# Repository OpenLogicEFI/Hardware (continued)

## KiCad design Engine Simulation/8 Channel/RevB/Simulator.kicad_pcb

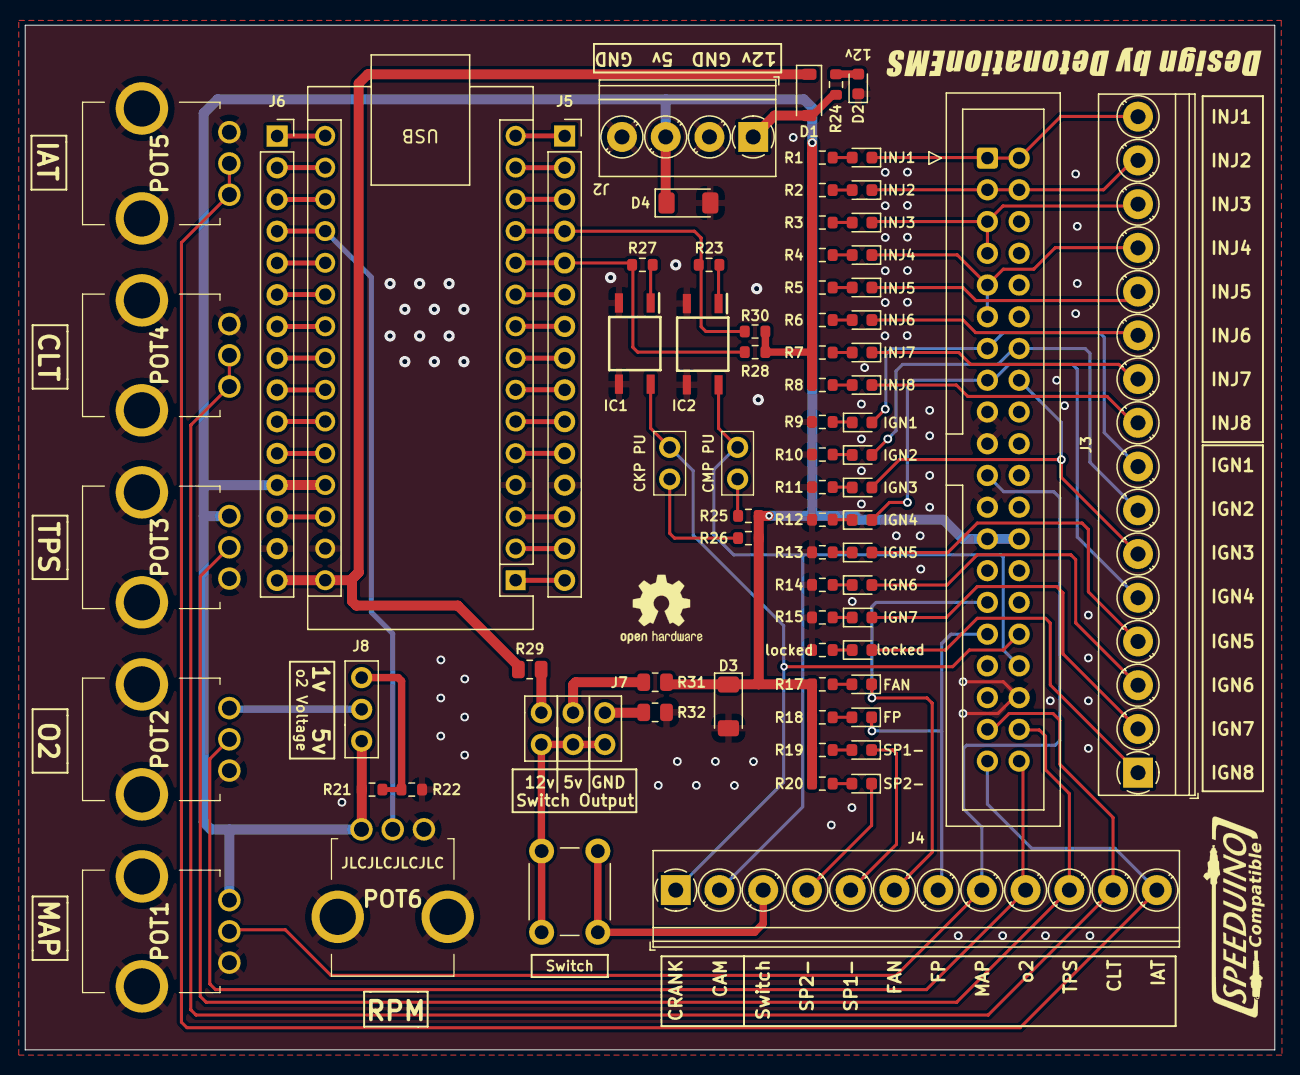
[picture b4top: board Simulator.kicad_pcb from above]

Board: 2 copper layers, 100.0 x 82.0 mm, 79 parts (0 on the bottom side), 89 nets.

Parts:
A1: Arduino_Nano_v3.x; Arduino_Nano
D1: B5819W; D_SOD-123
D2: 12v; LED_0603_1608Metric
D3, D4: ZMM5V6; D_MiniMELF
G1: Logo_Open_Hardware_Small; Design by 30mm
G2: Logo_Open_Hardware_Small; SpeeduinoCompatible-17mm
G3: Logo_Open_Hardware_Small; OSHW-Logo2_7.3x6mm_SilkScreen
IC1, IC2: EL357NB_TA_-G; SOP254P700X200-4N
J1: Conn_02x20_Counter_Clockwise; IDC-Header_2x20_P2.54mm_Vertical_Speeduino
J2: Conn_01x04; TerminalBlock_Phoenix_PT-1,5-4-3.5-H_1x04_P3.50mm_Horizontal
J3: Conn_01x08; TerminalBlock_Phoenix_PT-1,5-16-3.5-H_1x16_P3.50mm_Horizont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
J4: Conn_01x10; TerminalBlock_Phoenix_PT-1,5-12-3.5-H_1x12_P3.50mm_Horizont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
J5, J6: Conn_01x04; PinSocket_1x15_P2.54mm_Vertical
J7: Conn_01x03; PinSocket 2x03
J8: Conn_01x03; 3-PinSwitch
J9: CKP PU; 1x02-Proto
J10: CMP PU; 1x02-Proto
LED1: INJ1; LED_0603_1608Metric
LED2: INJ2; LED_0603_1608Metric
LED3: INJ3; LED_0603_1608Metric
LED4: INJ4; LED_0603_1608Metric
LED5: INJ5; LED_0603_1608Metric
LED6: INJ6; LED_0603_1608Metric
LED7: INJ7; LED_0603_1608Metric
LED8: INJ8; LED_0603_1608Metric
LED9: IGN1; LED_0603_1608Metric
LED10: IGN2; LED_0603_1608Metric
LED11: IGN3; LED_0603_1608Metric
LED12: IGN4; LED_0603_1608Metric
LED13: IGN5; LED_0603_1608Metric
LED14: IGN6; LED_0603_1608Metric
LED15: IGN7; LED_0603_1608Metric
LED16: locked; LED_0603_1608Metric
LED17: FAN; LED_0603_1608Metric
LED18: FP; LED_0603_1608Metric
LED19: SP1-; LED_0603_1608Metric
LED20: SP2-; LED_0603_1608Metric
POT1: IAT; RV09AF4020KB10K
POT2: CLT; RV09AF4020KB10K
POT3: MAP/SP1; RV09AF4020KB10K
POT4: TPS; RV09AF4020KB10K
POT5: o2; RV09AF4020KB10K
POT6: RPM; RV09AF4020KB10K
R1, R2, R3, R4, R5, R6, R7, R8, R9, R10, R11, R12, R13, R14, R15, R17, R18, R19, R20, R24, R25, R26, R28, R30: 1k; R_0603_1608Metric
R21, R23, R27: 470r; R_0603_1608Metric
R22: 100r; R_0603_1608Metric
R29, R31, R32: 0r; R_0805_2012Metric
SW1: Switch; SW_PUSH_6mm_H9.5mm
locked: 1k; R_0603_1608Metric

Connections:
12v-Unprotected: D1.2 (A), J2.1, R24.1
+3.3V: A1.17 (3V3), J6.2
+5V: A1.27 (+5V), D3.1 (K), D4.1 (K), J1.13, J1.28, J2.3, J6.12, J8.1, POT1.3, POT3.3, POT6.3, R1.1, R2.1, R3.1, R4.1, R5.1, R6.1, R7.1, R8.1, R17.1, R18.1, R19.1, R20.1, R21.1, R25.1, R26.1, R28.2, R30.2, R31.2
+12V: A1.30 (VIN), D1.1 (K), J6.15, R29.2
CAM: A1.12 (D9), J5.4, R23.2, R30.1
CAM-OUT: IC2.4 (C), J1.24, J4.2, J10.2
CLT: J1.19, J4.11, POT4.1, POT4.2
CRANK: A1.11 (D8), J5.5, R27.2, R28.1
CRANK-OUT: IC1.4 (C), J1.25, J4.1, J9.2
FAN: J1.15, J4.6, LED17.1 (K)
FP: J1.16, J4.7, LED18.1 (K)
GND: A1.4 (GND), A1.29 (GND), D2.1 (K), D3.2 (A), D4.2 (A), IC1.2 (K), IC1.3 (E), IC2.2 (K), IC2.3 (E), J1.9, J1.10, J1.12, J1.23, J2.2, J2.4, J5.12, J6.14, POT1.1, POT1.4 (Mounting_Tap), POT1.5 (Mounting_Tap), POT2.1, POT2.4 (Mounting_Tap), POT2.5 (Mounting_Tap), POT3.1, POT3.4 (Mounting_Tap), POT3.5 (Mounting_Tap), POT4.3, POT4.4 (Mounting_Tap), POT4.5 (Mounting_Tap), POT5.3, POT5.4 (Mounting_Tap), POT5.5 (Mounting_Tap), POT6.1, POT6.4 (Mounting_Tap), POT6.5 (Mounting_Tap), R9.1, R10.1, R11.1, R12.1, R13.1, R14.1, R15.1, R22.2, R32.1, locked.1
IAT: J1.20, J4.12, POT5.1, POT5.2
IGN1: J1.7, J3.8, LED9.2 (A)
IGN2: J1.34, J3.7, LED10.2 (A)
IGN3: J1.33, J3.6, LED11.2 (A)
IGN4: J1.8, J3.5, LED12.2 (A)
IGN5: J3.4, LED13.2 (A)
IGN6: J3.3, LED14.2 (A)
IGN7: J3.2, LED15.2 (A)
IGN8: J3.1, LED16.2 (A)
INJ1: J1.1, J1.40, J3.16, LED1.1 (K)
INJ2: J1.2, J1.39, J3.15, LED2.1 (K)
INJ3: J1.3, J1.4, J3.14, LED3.1 (K)
INJ4: J1.5, J1.6, J3.13, LED4.1 (K)
INJ5: J3.12, LED5.1 (K)
INJ6: J3.11, LED6.1 (K)
INJ7: J3.10, LED7.1 (K)
INJ8: J3.9, LED8.1 (K)
MAP: J1.11, J4.8, POT1.2
MC-A0: A1.19 (A0), J6.4, POT6.2
MC-A1: A1.20 (A1), J6.5
MC-A2: A1.21 (A2), J6.6
MC-A3: A1.22 (A3), J6.7
MC-A4: A1.23 (A4), J6.8
MC-A5: A1.24 (A5), J6.9
MC-A6: A1.25 (A6), J6.10
MC-A7: A1.26 (A7), J6.11
MC-AREF: A1.18 (AREF), J6.3
MC-D0: A1.2 (D0/RX), J5.14
MC-D1: A1.1 (D1/TX), J5.15
MC-D2: A1.5 (D2), J5.11
MC-D3: A1.6 (D3), J5.10
MC-D4: A1.7 (D4), J5.9
MC-D5: A1.8 (D5), J5.8
MC-D6: A1.9 (D6), J5.7
MC-D7: A1.10 (D7), J5.6
MC-D10: A1.13 (D10), J5.3
MC-D11: A1.14 (D11), J5.2
MC-D12: A1.15 (D12), J5.1
MC-D13: A1.16 (D13), J6.1
MC-RESET-3: A1.3 (~RESET), J5.13
MC-RESET-28: A1.28 (~RESET), J6.13
unnamed: D2.2 (A), R24.2
unnamed: IC1.1 (A), R27.1
unnamed: IC2.1 (A), R23.1
unnamed: J7.1, R29.1
unnamed: J7.2, J7.4, J7.6, SW1.2 (B)
unnamed: J7.3, R31.1
unnamed: J7.5, R32.2
unnamed: J8.3, R21.2, R22.1
unnamed: J9.1, R26.2
unnamed: J10.1, R25.2
unnamed: LED1.2 (A), R1.2
unnamed: LED2.2 (A), R2.2
unnamed: LED3.2 (A), R3.2
unnamed: LED4.2 (A), R4.2
unnamed: LED5.2 (A), R5.2
unnamed: LED6.2 (A), R6.2
unnamed: LED7.2 (A), R7.2
unnamed: LED8.2 (A), R8.2
unnamed: LED9.1 (K), R9.2
unnamed: LED10.1 (K), R10.2
unnamed: LED11.1 (K), R11.2
unnamed: LED12.1 (K), R12.2
unnamed: LED13.1 (K), R13.2
unnamed: LED14.1 (K), R14.2
unnamed: LED15.1 (K), R15.2
unnamed: LED16.1 (K), locked.2
unnamed: LED17.2 (A), R17.2
unnamed: LED18.2 (A), R18.2
unnamed: LED19.2 (A), R19.2
unnamed: LED20.2 (A), R20.2
SP1-: J4.5, LED19.1 (K)
SP2-: J4.4, LED20.1 (K)
SWITCH: J4.3, SW1.1 (A)
TPS: J1.22, J4.10, POT3.2
o2: J1.21, J4.9, POT2.2
o2-Voltage: J8.2, POT2.3
